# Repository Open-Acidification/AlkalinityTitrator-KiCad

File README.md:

# AlkalinityTitrator-KiCad
<!-- ALL-CONTRIBUTORS-BADGE:START - Do not remove or modify this section -->

<!-- ALL-CONTRIBUTORS-BADGE:END -->

KiCad files for pcb design for Open Acidification Alkalinity Titrator unit.

## Software Requirements

1. [KiCad](https://kicad.org/) - The PCB layout was created with KiCad which works on multiple platforms.

## Viewing and Editing the Schematic

1. Clone this repo to your local computer.
1. Open KiCad.
1. Use the KiCad menu to open the `full_project.pro` project file.
    * _File -> Open Project_
    * Navigate to your local repo location and select `full_project.pro` project file.
    * Double click the `full_project.sch` file on the left pane to open Eeschema.
1. View the Schematic.

## Viewing and Editing the PCB

1. Clone this repo to your local computer.
1. Open KiCad.
1. Use the KiCad menu to open the `full_project.pro` project file.
    * _File -> Open Project_
    * Navigate to your local repo location and select `full_project.pro` project file.
    * Double click the `full_project.kicad_pcb` file on the left pane to open Pcbnew.
1. View the PCB.

## Release

Each release has the appropriate binary Gerber (`.gbr`) and Drill (`.drl`) to be sent to the PCB board printing company.

We may have extra printed. Please contact us.

## Related Projects

* Micro Controller - [Alkalinity Titrator](https://github.com/Open-Acidification/AlkalinityTitrator) forms the brain of the device.
* PCB - __This repo__ holds the specifications for the PCB which connects various sensors.

## Contributors ✨

Thanks goes to these wonderful people ([emoji key](https://allcontributors.org/docs/en/emoji-key)):

<!-- ALL-CONTRIBUTORS-LIST:START - Do not remove or modify this section -->
<!-- prettier-ignore-start -->
<!-- markdownlint-disable -->
<table>
  <tr>
    <td align="center"><a href="https://github.com/KonradMcClure"><br /><sub><b>Konrad McClure</b></sub></a><br /><a href="https://github.com/Open-Acidification/AlkalinityTitrator-KiCad/commits?author=KonradMcClure" title="Code">💻</a></td>
    <td align="center"><a href="https://github.com/Noah-Griffith"><br /><sub><b>Noah-Griffith</b></sub></a><br /><a href="https://github.com/Open-Acidification/AlkalinityTitrator-KiCad/commits?author=Noah-Griffith" title="Code">💻</a></td>
  </tr>
</table>

<!-- markdownlint-restore -->
<!-- prettier-ignore-end -->

<!-- ALL-CONTRIBUTORS-LIST:END -->

This project follows the [all-contributors](https://github.com/all-contributors/all-contributors) specification. Contributions of any kind welcome!

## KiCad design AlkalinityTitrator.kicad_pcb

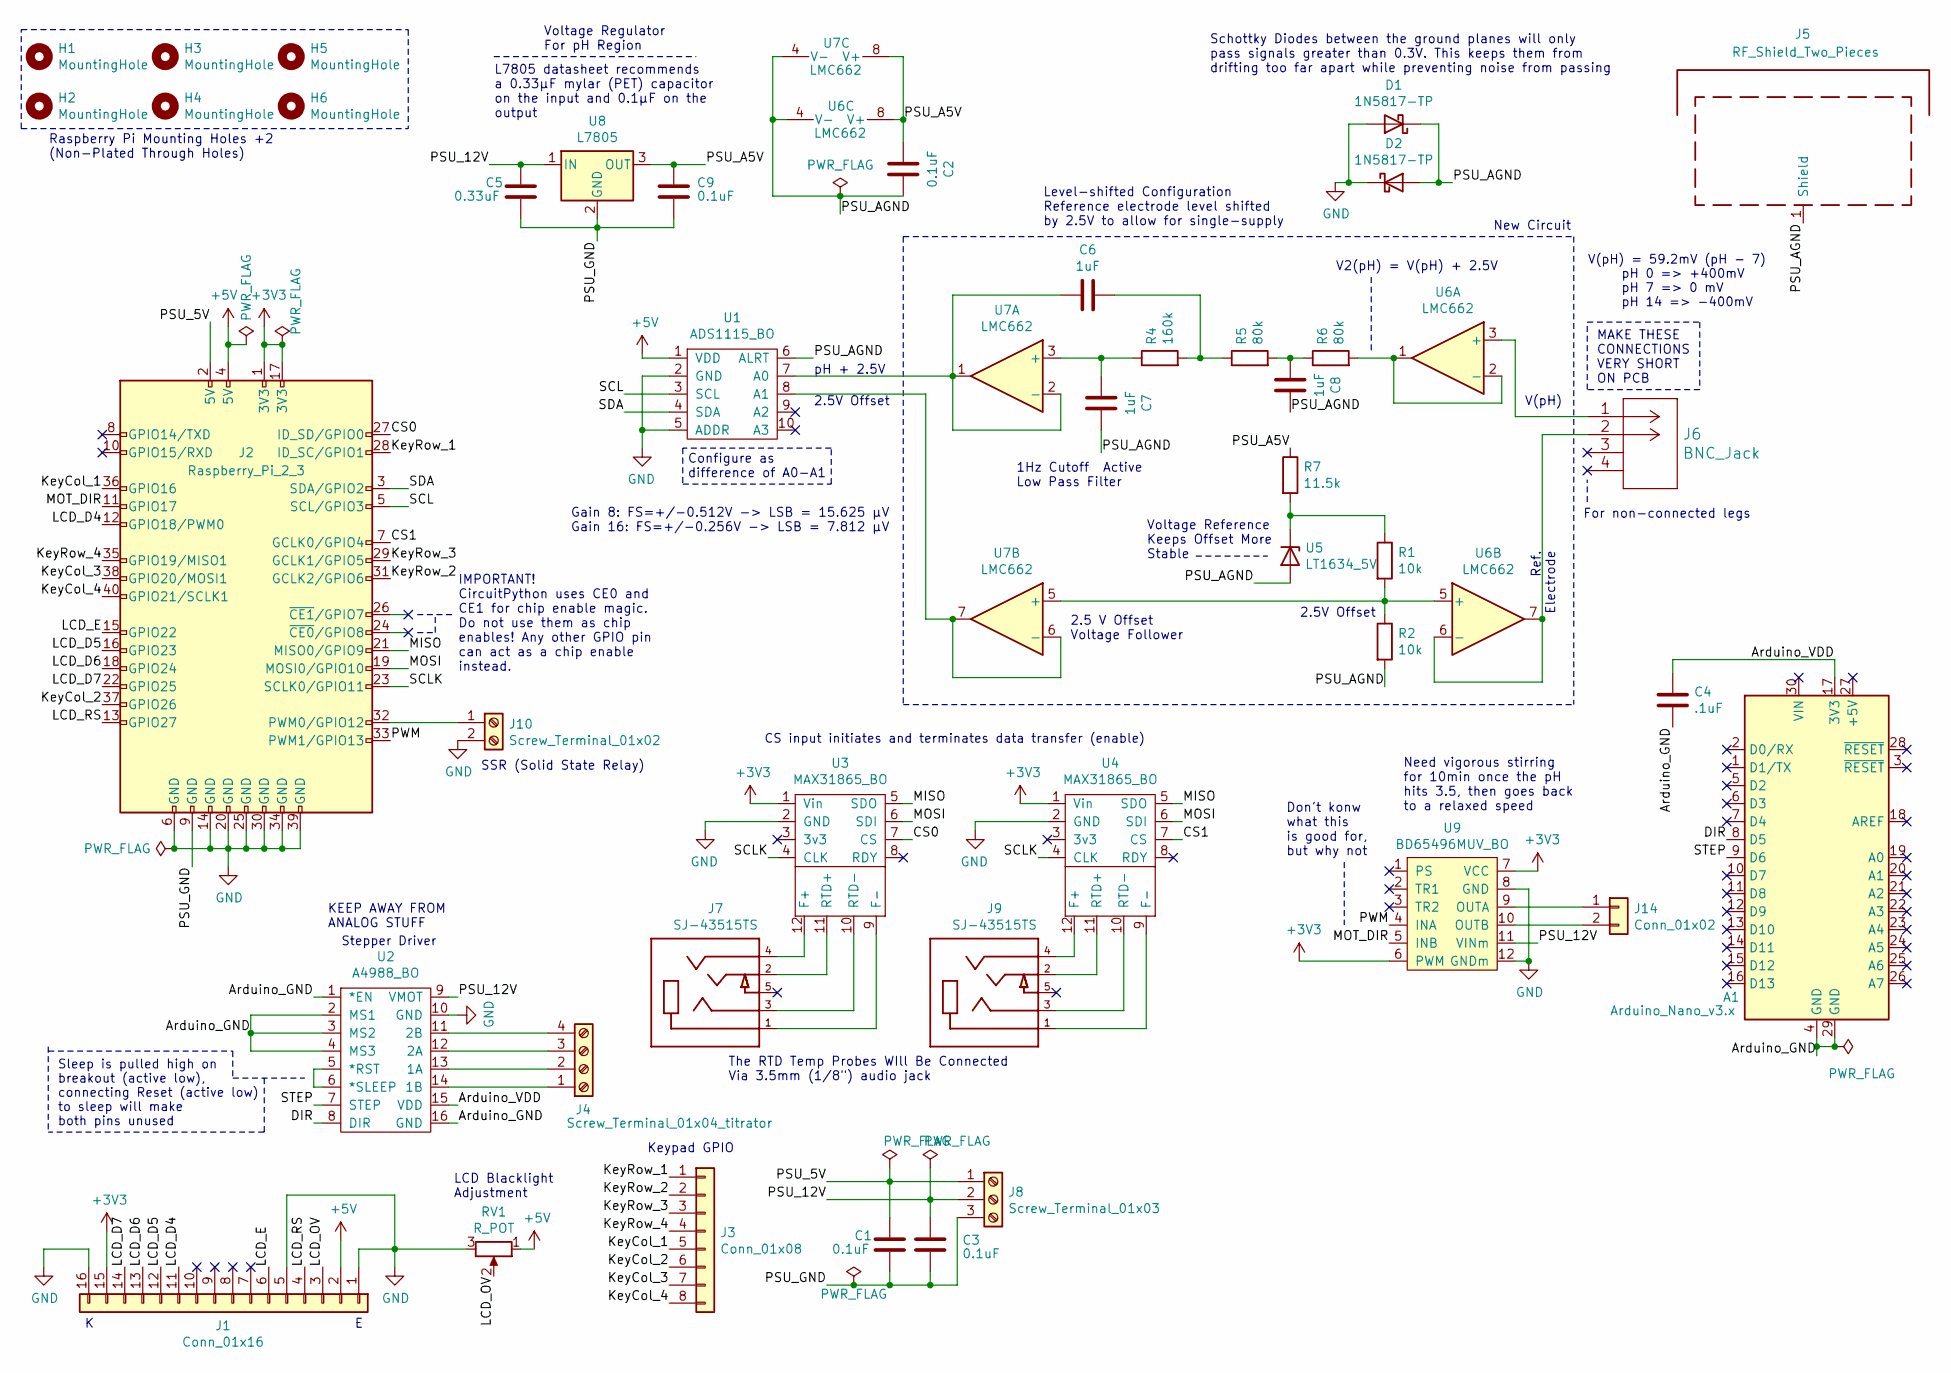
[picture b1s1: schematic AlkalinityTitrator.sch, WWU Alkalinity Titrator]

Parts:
A1: Arduino_Nano_v3.x; Arduino_Nano
C1, C2, C3: 0.1uF; C_Disc_D3.8mm_W2.6mm_P2.50mm
C4: .1uF; C_Disc_D3.8mm_W2.6mm_P2.50mm
C5: 0.33uF; C_Rect_L7.2mm_W3.5mm_P5.00mm_FKS2_FKP2_MKS2_MKP2
C6, C7, C8: 1uF; C_Disc_D3.8mm_W2.6mm_P2.50mm
C9: 0.1uF; C_Rect_L7.2mm_W3.5mm_P5.00mm_FKS2_FKP2_MKS2_MKP2
D1, D2: 1N5817-TP; D_DO-41_SOD81_P7.62mm_Horizontal
H1, H2, H3, H4, H5, H6: MountingHole; MountingHole_3mm
J1: Conn_01x16; PinHeader_1x16_P2.54mm_Horizontal
J2: Raspberry_Pi_2_3; RaspberryPi
J3: Conn_01x08; PinHeader_1x08_P2.54mm_Horizontal
J4: Screw_Terminal_01x04_titrator; TerminalBlock_bornier-4_P5.08mm
J5: RF_Shield_Two_Pieces; SMS-205_LeaderTech_RFShield
J6: BNC_Jack
J7, J9: SJ-43515TS; CUI_SJ-43515TS; PART_REV 1.04
J8: Screw_Terminal_01x03; TerminalBlock_bornier-3_P5.08mm
J10: Screw_Terminal_01x02; TerminalBlock_bornier-2_P5.08mm
J14: Conn_01x02; PinHeader_1x02_P2.54mm_Horizontal
R1, R2: 10k; R_Axial_DIN0207_L6.3mm_D2.5mm_P7.62mm_Horizontal
R4: 160k; R_Axial_DIN0207_L6.3mm_D2.5mm_P7.62mm_Horizontal
R5, R6: 80k; R_Axial_DIN0207_L6.3mm_D2.5mm_P7.62mm_Horizontal
R7: 11.5k; R_Axial_DIN0207_L6.3mm_D2.5mm_P7.62mm_Horizontal
RV1: R_POT; Potentiometer_Piher_PT-6-V_Vertical
U1: ADS1115_BO; ADS1115_BO_Footprint
U2: A4988_BO; A4988_BO_Footprint
U3, U4: MAX31865_BO; MAX31865
U5: LT1634_5V; TO-92_Inline
U6, U7: LMC662; DIP-8_W7.62mm
U8: L7805; 78XXS
U9: BD65496MUV_BO; BD65496MUV_BO_Footprint

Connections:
+3V3: J1.15, J2.1 (3V3), J2.17 (3V3), U3.1 (Vin), U4.1 (Vin), U9.6 (PWM), U9.7 (VCC)
+5V: J1.2, J2.4 (5V), RV1.1, U1.1 (VDD)
/Arduino_GND: A1.4 (GND), A1.29 (GND), C4.2, U2.1 (*EN), U2.2 (MS1), U2.3 (MS2), U2.4 (MS3), U2.16 (GND)
/Arduino_VDD: A1.17 (3V3), C4.1, U2.15 (VDD)
/CS0: J2.27 (ID_SD/GPIO0), U3.7 (CS)
/CS1: J2.7 (GCLK0/GPIO4), U4.7 (CS)
/DIR: A1.8 (D5), U2.8 (DIR)
/KeyCol_1: J2.36 (GPIO16), J3.5
/KeyCol_2: J2.37 (GPIO26), J3.6
/KeyCol_3: J2.38 (GPIO20/MOSI1), J3.7
/KeyCol_4: J2.40 (GPIO21/SCLK1), J3.8
/KeyRow_1: J2.28 (ID_SC/GPIO1), J3.1
/KeyRow_2: J2.31 (GCLK2/GPIO6), J3.2
/KeyRow_3: J2.29 (GCLK1/GPIO5), J3.3
/KeyRow_4: J2.35 (GPIO19/MISO1), J3.4
/LCD_D4: J1.11, J2.12 (GPIO18/PWM0)
/LCD_D5: J1.12, J2.16 (GPIO23)
/LCD_D6: J1.13, J2.18 (GPIO24)
/LCD_D7: J1.14, J2.22 (GPIO25)
/LCD_E: J1.6, J2.15 (GPIO22)
/LCD_OV: J1.3, RV1.2
/LCD_RS: J1.4, J2.13 (GPIO27)
/MISO: J2.21 (MISO0/GPIO9), U3.5 (SDO), U4.5 (SDO)
/MOSI: J2.19 (MOSI0/GPIO10), U3.6 (SDI), U4.6 (SDI)
/MOT_DIR: J2.11 (GPIO17), U9.5 (INB)
/PSU_5V: C1.1, J2.2 (5V), J8.1
/PSU_12V: C3.1, C5.1, J8.2, U2.9 (VMOT), U8.1 (IN), U9.11 (VINm)
/PSU_A5V: C2.1, C9.1, R7.1, U6.8 (V+), U7.8 (V+), U8.3 (OUT)
/PSU_AGND: C2.2, C7.2, C8.2, D1.1 (K), D2.2 (A), J5.1, R2.2, U1.6 (ALRT), U5.1 (A), U6.4 (V-), U7.4 (V-)
/PSU_GND: C1.2, C3.2, C5.2, C9.2, J2.9 (GND), J8.3, U8.2 (GND)
/PWM: J2.33 (PWM1/GPIO13), U9.4 (INA)
/SCL: J2.5 (SCL/GPIO3), U1.3 (SCL)
/SCLK: J2.23 (SCLK0/GPIO11), U3.4 (CLK), U4.4 (CLK)
/SDA: J2.3 (SDA/GPIO2), U1.4 (SDA)
/STEP: A1.9 (D6), U2.7 (STEP)
GND: D1.2 (A), D2.1 (K), J1.1, J1.5, J1.16, J2.6 (GND), J2.14 (GND), J2.20 (GND), J2.25 (GND), J2.30 (GND), J2.34 (GND), J2.39 (GND), J10.2, RV1.3, U1.2 (GND), U1.5 (ADDR), U2.10 (GND), U3.2 (GND), U4.2 (GND), U9.8 (GND), U9.12 (GNDm)
unnamed: C6.1, U1.7 (A0), U7.1, U7.2 (-)
unnamed: C6.2, R4.2, R5.1
unnamed: C7.1, R4.1, U7.3 (+)
unnamed: C8.1, R5.2, R6.1
unnamed: J4.1 (2B), U2.14 (1B)
unnamed: J4.2 (2A), U2.13 (1A)
unnamed: J4.3 (1A), U2.12 (2A)
unnamed: J4.4 (1B), U2.11 (2B)
unnamed: J6.1, U6.3 (+)
unnamed: J6.2, U6.6 (-), U6.7
unnamed: J7.1, U3.9 (F-)
unnamed: J7.2, U3.11 (RTD+)
unnamed: J7.3, U3.10 (RTD-)
unnamed: J7.4, U3.12 (F+)
unnamed: J9.1, U4.9 (F-)
unnamed: J9.2, U4.11 (RTD+)
unnamed: J9.3, U4.10 (RTD-)
unnamed: J9.4, U4.12 (F+)
unnamed: J2.32 (PWM0/GPIO12), J10.1
unnamed: J14.1, U9.9 (OUTA)
unnamed: J14.2, U9.10 (OUTB)
unnamed: R1.1, R7.2, U5.2 (K)
unnamed: R1.2, R2.1, U6.5 (+), U7.5 (+)
unnamed: R6.2, U6.1, U6.2 (-)
unnamed: U1.8 (A1), U7.6 (-), U7.7
unnamed: U2.5 (*RST), U2.6 (*SLEEP)

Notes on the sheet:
Stepper Driver
Sleep is pulled high on breakout (active low), connecting Reset (active low) to sleep will make both pins unused
Need vigorous stirring for 10min once the pH hits 3.5, then goes back to a relaxed speed
KEEP AWAY FROM ANALOG STUFF
Gain 8: FS=+/-0.512V -> LSB = 15.625 μV Gain 16: FS=+/-0.256V -> LSB = 7.812 μV
Level-shifted Configuration Reference electrode level shifted by 2.5V to allow for single-supply
MAKE THESE CONNECTIONS VERY SHORT ON PCB
V(pH) = 59.2mV (pH - 7) pH 0 => +400mV pH 7 => 0 mV pH 14 => -400mV
V2(pH) = V(pH) + 2.5V
Ref. Electrode
V(pH)
New Circuit
Keypad GPIO
LCD Blacklight Adjustment
CS input initiates and terminates data transfer (enable)
Raspberry Pi Mounting Holes +2 (Non-Plated Through Holes)
The RTD Temp Probes WIll Be Connected Via 3.5mm (1/8") audio jack
SSR (Solid State Relay)
IMPORTANT! CircuitPython uses CE0 and CE1 for chip enable magic. Do not use them as chip enables! Any other GPIO pin can act as a chip enable instead.
pH + 2.5V
2.5V Offset
2.5 V Offset Voltage Follower
Configure as difference of A0-A1
1Hz Cutoff Active Low Pass Filter
Voltage Regulator For pH Region
Voltage Reference Keeps Offset More Stable
Don't konw what this is good for, but why not
For non-connected legs
Schottky Diodes between the ground planes will only pass signals greater than 0.3V. This keeps them from drifting too far apart while preventing noise from passing
L7805 datasheet recommends a 0.33μF mylar (PET) capacitor on the input and 0.1μF on the output

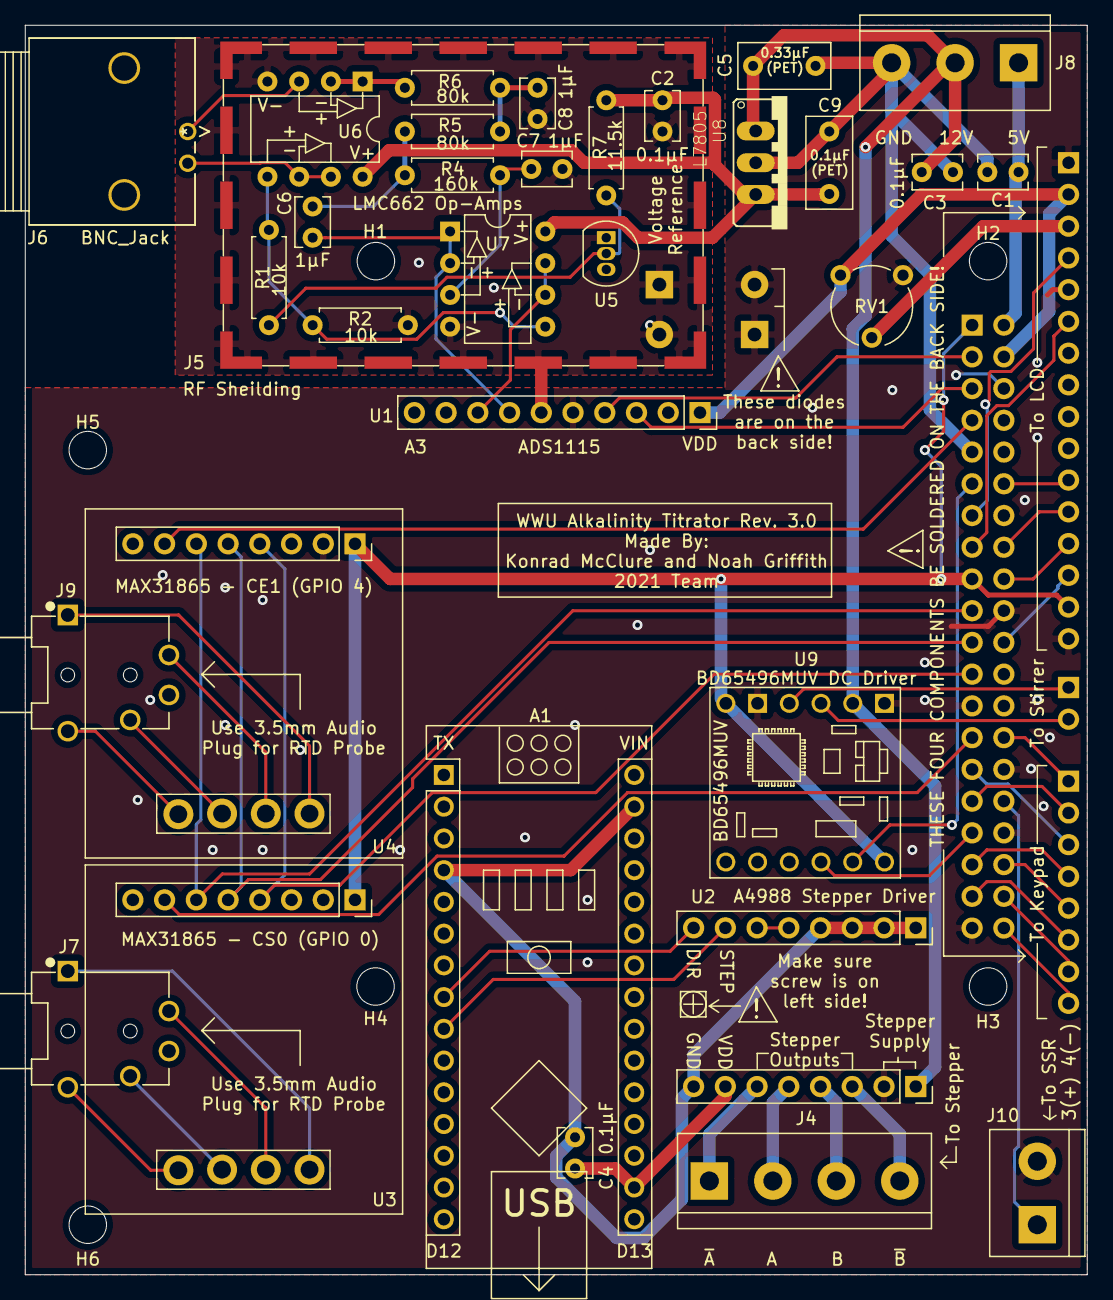
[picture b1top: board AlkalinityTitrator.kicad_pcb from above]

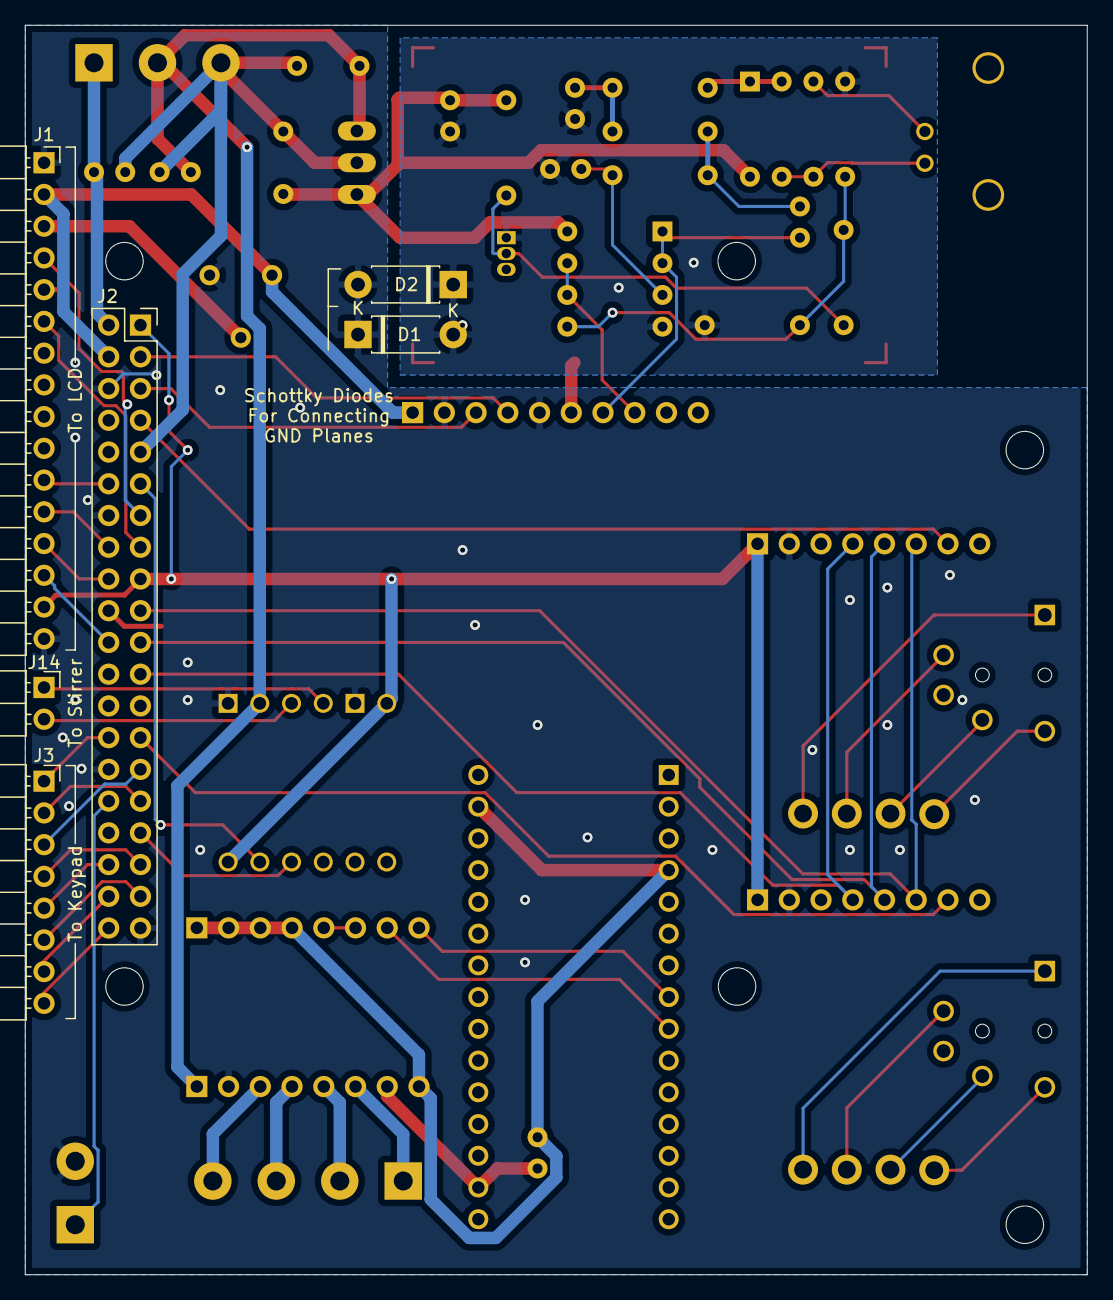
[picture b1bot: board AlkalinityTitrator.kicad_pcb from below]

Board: 2 copper layers, 85.0 x 100.0 mm, 45 parts (6 on the bottom side), 62 nets.

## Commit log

2021-02-08 Initial open source related files.
2021-02-12 Added current schematic version, layout not updated
2021-02-12 Added schematic instructions to readme
2021-02-23 Added B and C components to LPF opamp circuit
2021-03-01 Used git like a big boy
2021-03-01 updated linear regulator footprint
2021-03-01 Added RF Shield footprint
2021-03-01 made rf shield footprint smaller
2021-03-01 New RF Shield footprint
2021-03-01 Added LCD and Keypad connectors, switched PSU connector to screw terminal, updated footprints, and added datasheets to parts.
2021-03-01 layed out PCB
2021-03-01 fixed screw terminal placement and ground plane overlaps
2021-03-02 added low pass filter fix on schematic and pcb
2021-03-02 Added 3d model directory and added models to the footprints
2021-03-06 Changed connectors and made a few small updates. Changed series voltage reference to shunt
2021-03-06 help
2021-03-06 Switched GPIO on rasp. π for better routing, added in all 3d models
2021-03-06 I made a colander
2021-03-06 Routed :)
2021-03-07 nothing changed just don
2021-03-08 Silkscreening and most final adjustments done
2021-03-08 Small silkscreen edits
2021-03-08 Label 1x1 pin
2021-03-08 No changes, just don't want git to freak out
2021-03-08 please let me sleep
2021-03-09 here
2021-03-09 Extended board, added MAX31685 footprint for new mounting style, added 3.5mm audio jacks, cried a little
2021-03-09 not much
2021-03-09 Added interactive BOM
2021-03-09 It works now, fix any complaints
2021-03-09 filled in zone and remade interactive BOM
2021-03-09 Added in screw terminal 3d models, adjusted screw terminal position slightly, generated gerbers
2021-03-10 Erased obsolete drawing
2021-03-22 Fixed silkscreen...again
2021-03-23 cache and stuff
2021-05-02 Please just push
2021-05-02 Added offset voltage follower for ADC in schematic, added extra notes
2021-05-11 Changed diode footprint
2021-05-27 I don't want github to throw a fit
2021-06-09 Rev 3 schematic update, expanded footprint library for custom models
2021-06-09 Finally changed that stupid project name
2021-06-09 rcb rev 3 start
2021-06-09 sleep is for losers. Did layout for Rev 3 board
2021-06-09 Fixed weird ground plane
2021-06-10 Finished Rev3, added silkscreen, added voltage reference capacitors, generated gerbers and drills
2021-06-10 Fixed gerbers, for some reason more generated and looked like a 4 layer board
2021-06-16 Cleaning up repo
2021-06-16 Cleaned up repo
2021-06-17 Revision 3 (#2)
    Built off of the original Revision 1 (and an intermediary Rev 2) of the Alkalinity Titrator PCB.
    * Expanded PCB to include all breakout boards and appropriate interfacing
    * Reworked the pH probe circuit to increase resistance to noise and increase precision
    * Changed PT1000 connections to 3.5mm jack interface
    * Added BD65496MUV dc motor driver for magnetic stirrer
    * Added LCD, keypad, and magnetic stirrer components
2021-06-29 docs: update README.md [skip ci]
2021-06-29 docs: create .all-contributorsrc [skip ci]
2021-06-29 docs: add KonradMcClure as a contributor for code (#3)
    * docs: update README.md [skip ci]
    * docs: create .all-contributorsrc [skip ci]
2021-06-29 docs: update .all-contributorsrc [skip ci]
2021-06-29 docs: add Noah-Griffith as a contributor for code (#4)
    * docs: update README.md [skip ci]
    * docs: update .all-contributorsrc [skip ci]
2021-08-25 Update LICENSE
    Switch to CERN-OHL-W license.

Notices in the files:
parts and their libraries:
Copyright 2016 Accelerated Designs. All rights reserved.
